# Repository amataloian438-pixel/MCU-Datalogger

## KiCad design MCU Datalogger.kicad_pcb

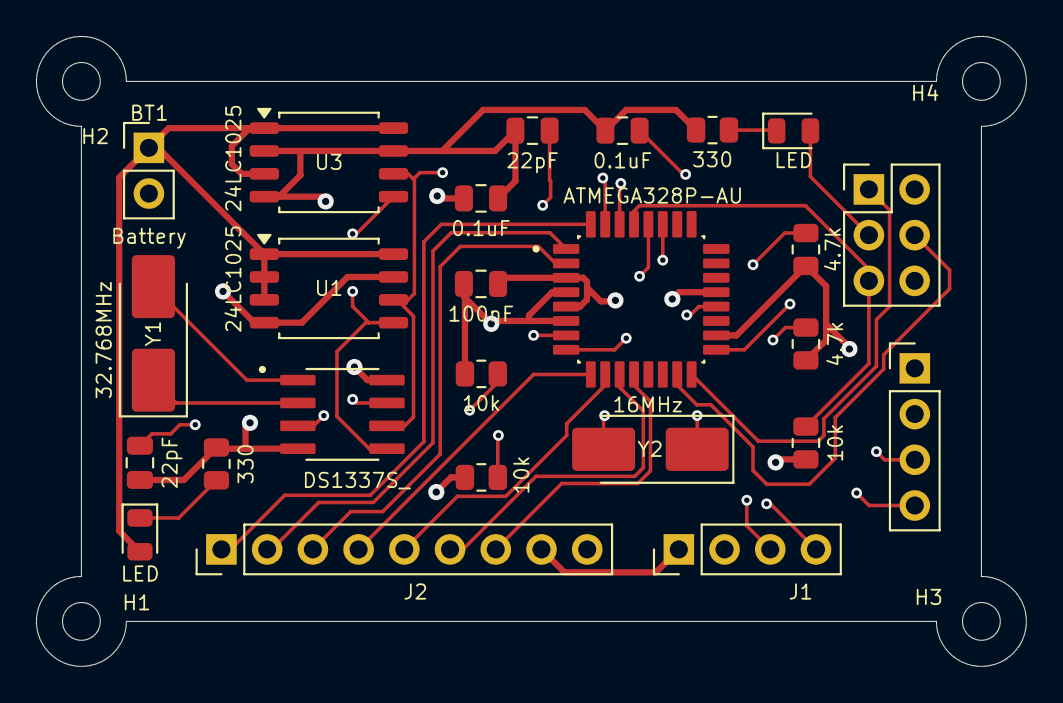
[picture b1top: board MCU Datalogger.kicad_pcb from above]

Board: 4 copper layers, 55.0 x 35.0 mm, 29 parts (0 on the bottom side), 26 nets.

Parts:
BT1: Battery; PinHeader_1x02_P2.54mm_Vertical
C1, C2: 22pF; C_0805_2012Metric
C3: 100nF; C_0805_2012Metric
C4, C5: 0.1uF; C_0805_2012Metric
D1, D2: LED; LED_0805_2012Metric
H1, H2, H3, H4: MountingHole; MountingHole_2.1mm
J1, J3: Conn_01x04_Pin; PinHeader_1x04_P2.54mm_Vertical
J2: Conn_01x09_Pin; PinHeader_1x09_P2.54mm_Vertical
J4: Conn_02x03_Odd_Even; PinHeader_2x03_P2.54mm_Vertical
R1, R4: 330; R_0805_2012Metric
R2, R3: 4.7k; R_0805_2012Metric
R5, R6, R7: 10k; R_0805_2012Metric
U1, U3: 24LC1025; SOIC-8_5.3x5.3mm_P1.27mm
U2: DS1337S_; SOIC127P600X175-8N
U4: ATMEGA328P-AU; QFP80P900X900X120-32N
Y1: 32.768MHz; Crystal_SMD_5032-2Pin_5.0x3.2mm_HandSoldering
Y2: 16MHz; Crystal_SMD_5032-2Pin_5.0x3.2mm_HandSoldering

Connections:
/D2: J2.1, U4.32 (PD2)
/D3: J2.2, U4.1 (PD3)
/D4: J2.3, U4.2 (PD4)
/D5: J2.4, U4.9 (PD5)
/D6: J2.5, U4.10 (PD6)
/D7: J2.6, U4.11 (PD7)
/D8: J2.7, U4.12 (PB0)
/MISO: J4.1, U4.16 (PB4)
/MOSI: J4.4, U4.15 (PB3)
/RESET: J4.5, R7.2, U4.29 (PC6/~RESET)
/RX: J3.3, U4.30 (PD0)
/SCK: D1.2 (A), J4.3, U4.17 (PB5)
/SCL: J1.4, R2.2, U1.6 (SCL), U2.6 (SCL), U3.6 (SCL), U4.28 (PC5)
/SDA: J1.3, R3.2, U1.5 (SDA), U2.5 (SDA), U3.5 (SDA), U4.27 (PC4)
/TX: J3.4, U4.31 (PD1)
GND: BT1.2 (-), C1.1, C2.1, C3.2, C4.1, C5.2, J1.1, J2.8, J3.1, J4.6, R1.2, R4.1, U1.4 (GND), U1.7 (WP), U2.4 (GND), U3.2 (A1), U3.4 (GND), U3.7 (WP), U4.3 (GND), U4.5 (GND), U4.21 (GND)
unnamed: D1.1 (K), R4.2
unnamed: D2.1 (K), R1.1
unnamed: R6.2, U2.7 (SQW/~INT)
unnamed: U2.1 (X1), Y1.2
unnamed: U2.2 (X2), Y1.1
unnamed: R5.2, U2.3 (~INTA)
unnamed: C4.2, U4.20 (AREF)
unnamed: C1.2, U4.7 (PB6), Y2.2
unnamed: C2.2, U4.8 (PB7), Y2.1
VCC: BT1.1 (+), C3.1, C5.1, D2.2 (A), J1.2, J2.9, J3.2, J4.2, R2.1, R3.1, R5.1, R6.1, R7.1, U1.1 (A0), U1.2 (A1), U1.3 (A2), U1.8 (VCC), U2.8 (VCC), U3.1 (A0), U3.3 (A2), U3.8 (VCC), U4.4 (VCC), U4.6 (VCC), U4.18 (AVCC)
